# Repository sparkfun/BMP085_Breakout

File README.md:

**NOTE:** *This product has been retired from our catalog. If you are looking for more up-to-date info, please check out some of these resources to see how other users are still hacking and improving on this product.*
* *[SparkFun Forum](https://forum.sparkfun.com/)*
* *[Comments Here on GitHub](https://github.com/sparkfun/BMP085_Breakout/issues)*

BMP085 Breakout
===============

*[BMP085 Breakout Board (SEN-11282)](https://www.sparkfun.com/products/11282)*

This is a breadboard friendly breakout board for the EOL'ed Bosch BMP085 high-precision, low-power digital barometer. 

Repository Contents
-------------------
* **/Firmware** - Example ATMega328 code and Arduino code to use with the sensor
* **/Hardware** - All Eagle design files (.brd, .sch)

Documentation
--------------
* **[Quickstart Guide](http://www.sparkfun.com/tutorials/253)** - Basic hookup guide.

License Information
-------------------
The hardware is released under [Creative Commons Share-alike 3.0](http://creativecommons.org/licenses/by-sa/3.0/).  
All other code is open source so please feel free to do anything you want with it; you buy me a beer if you use this and we meet someday ([Beerware license](http://en.wikipedia.org/wiki/Beerware)).

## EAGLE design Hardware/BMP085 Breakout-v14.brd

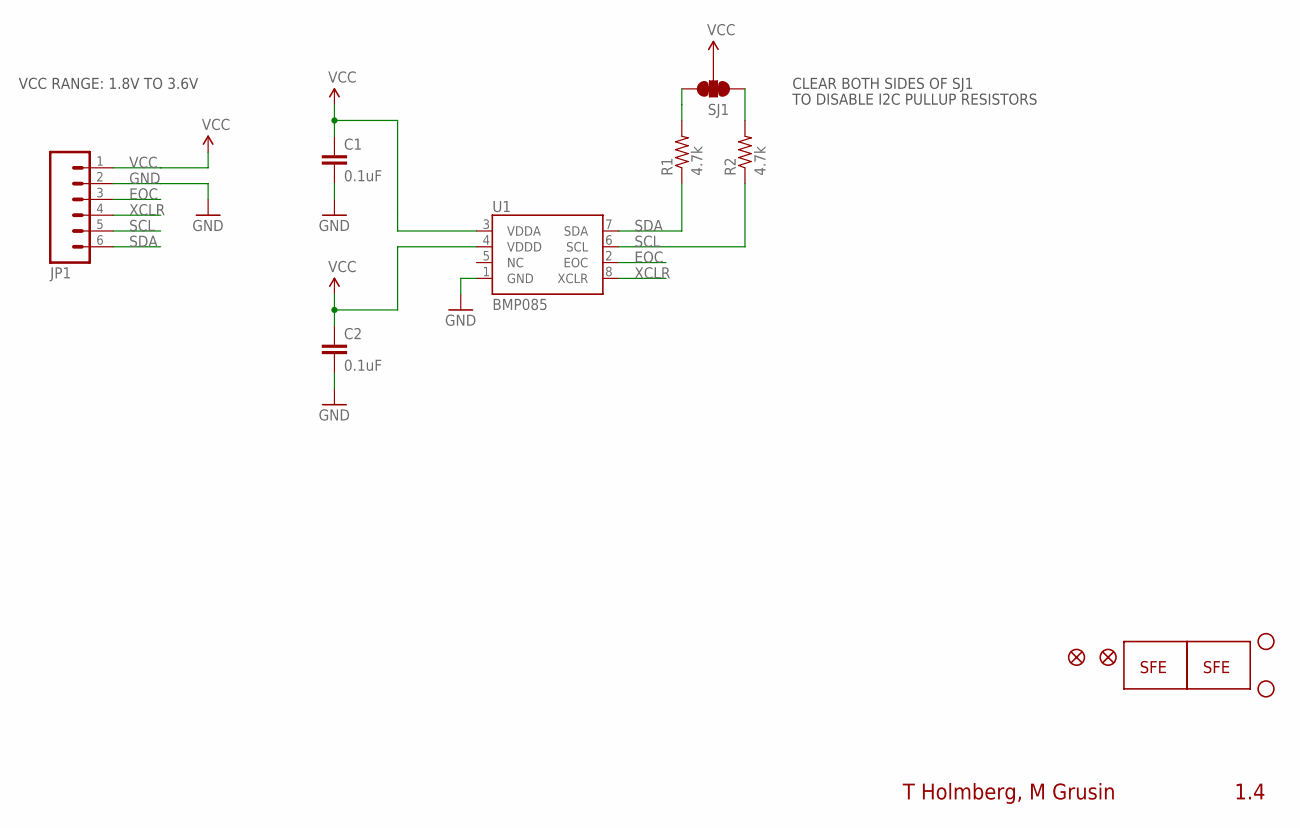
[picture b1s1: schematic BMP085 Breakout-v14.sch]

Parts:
C1, C2: 0.1uF; 0402-CAP
JP1: M06SIP; 1X06
JP2: LOGO-SFENW2; SFE-NEW-WEB
JP3, JP4: FIDUCIALUFIDUCIAL; MICRO-FIDUCIAL
LOGO1: LOGO-SFESK; SFE-LOGO-FLAME
R1, R2: 4.7k; 0402-RES
SJ1: SOLDERJUMPER_2WAYPASTE1&2&3; SJ_3_PASTE1&2&3
STANDOFF1, STANDOFF2: STAND-OFF
U1: BMP085

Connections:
EOC: JP1.3, U1.2 (EOC)
GND: C1.2, C2.2, JP1.2, U1.1 (GND)
unnamed: R1.2, SJ1.3
unnamed: R2.2, SJ1.1
SCL: JP1.5, R2.1, U1.6 (SCL)
SDA: JP1.6, R1.1, U1.7 (SDA)
VCC: C1.1, C2.1, JP1.1, SJ1.2, U1.3 (VDDA), U1.4 (VDDD)
XCLR: JP1.4, U1.8 (XCLR)

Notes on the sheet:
T Holmberg, M Grusin
1.4
CLEAR BOTH SIDES OF SJ1
TO DISABLE I2C PULLUP RESISTORS
VCC RANGE: 1.8V TO 3.6V

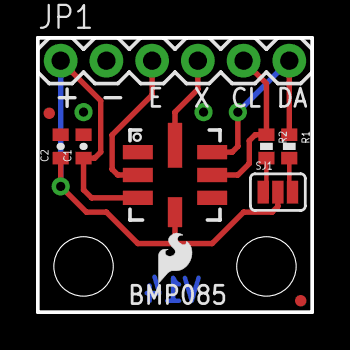
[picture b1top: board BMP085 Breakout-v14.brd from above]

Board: 2 copper layers, 15.2 x 15.2 mm, 13 parts (1 on the bottom side), 8 nets.

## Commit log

2013-09-03 Adding Firmware and Hardware files
2013-09-03 Update README.md
    Fixing typos
2020-05-22 Update BMP085_Arduino_Example.ino
    Removing lines based on feedback => https://github.com/sparkfun/BMP085_Breakout/issues/1 .

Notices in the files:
parts and their libraries:
SparkFun-Electromechanical: Licensing: CC v3.0 Share-Alike You are welcome to use this library for commercial purposes.
SparkFun-Aesthetics: Released under the Creative Commons
